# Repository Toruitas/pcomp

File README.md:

# Physical Computing 1

Msc Creative Computing 2019

Instructor: Phoenix Perry

By Stuart Leitch 

## Final Project:
Link: [Thinking Cap](https://github.com/Toruitas/thinkingcap)

## Homework & Labwork
[Week 1](https://github.com/Toruitas/pcomp/tree/master/wk01)

[Week 2](https://github.com/Toruitas/pcomp/tree/master/wk02)

[Week 3](https://github.com/Toruitas/pcomp/tree/master/wk03)

[Week 4](https://github.com/Toruitas/pcomp/tree/master/wk04)

Week 5 was pushed to week 6.

[Week 6](https://github.com/Toruitas/pcomp/tree/master/wk06)

[Week 7](https://github.com/Toruitas/pcomp/tree/master/wk07)

[Week 8 - group documentation of Feather](https://github.com/phoenixperry/cci-ual-pcomp/tree/master/week08/feather_docs)

[Week 9 - Eagle](https://github.com/Toruitas/pcomp/tree/master/wk09)

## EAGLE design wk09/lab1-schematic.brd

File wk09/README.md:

# Week 9 labs
Msc Creative Computing
Physical Computing #6 w/ Phoenix Perry
By Stuart Leitch
November 25, 2019

[Lecture PowerPoint](https://github.com/phoenixperry/cci-ual-pcomp/blob/master/week09/Tutorial_laserCutting.pdf)
[Lecture README](https://github.com/phoenixperry/cci-ual-pcomp/blob/master/week09/Week09.md)

## Lab #1: Learn Eagle via the tutorial

Eagle is a professional CAD software for designing circuitboards, which later go to fabrication. It's the next step beyond merely soldering.
Though it is professional, it doesn't actually install on Ubuntu. It just lives wherever you extract it to. 

Drawing a circuit was somewhat annoying, especially grabbing the center of each object to move or rotate. Still, given the large amount of obejcts included in the Sparkfun library, it was reasonably straightforward. Rather than use the suggested Arduino in the tutorial, I grabbed a MEGA from the collection to make things a bit more less copy and paste.

### The resulting circuit:

After drawing the circuit schematic, connecting the wires in a logical way proved to be its own challenge. Reminded me of those brain games where you have to route colored trains along tracks to their respective colored train garages. Eventually I got the whole circuit drawn on the board.

### The resulting board:

The primary question I have right now: Why is the board representation of the Arduino so dissimilar from the circuit diagram one? The only answer I can guess at is that this Arduino is only meant to be used on the circuit, and not used on the board side. In the future, when only using components, it may be clearer.

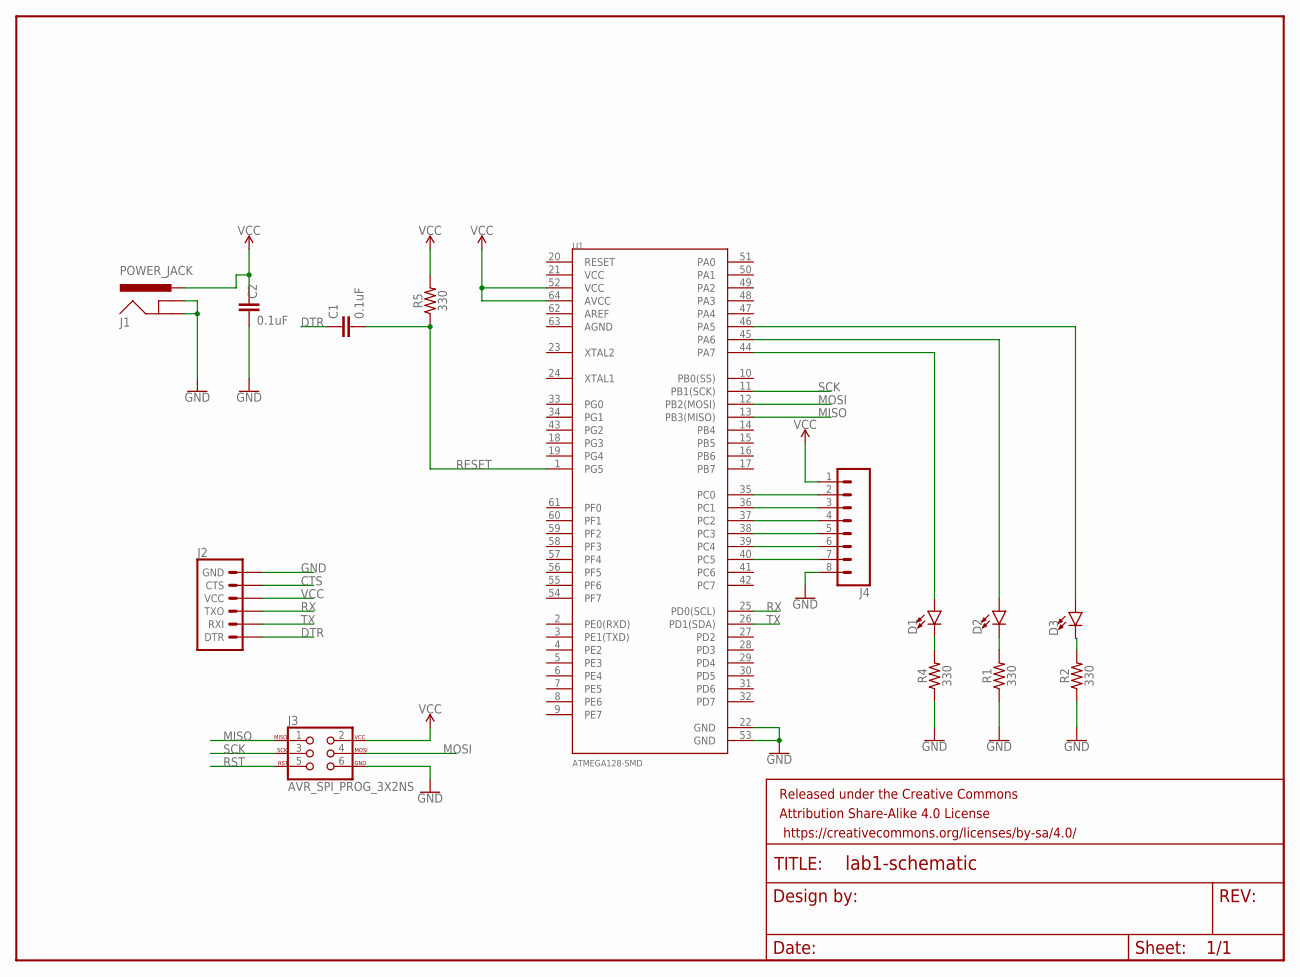
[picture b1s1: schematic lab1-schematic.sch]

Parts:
C1, C2: 0.1uF; CAP-PTH-SMALL-KIT
D1, D2, D3: LED3MM; LED_3MM
FRAME1: FRAME-LETTER; CREATIVE_COMMONS
J1: POWER_JACK; POWER_JACK_PTH
J2: 6_PIN_SERIAL_TARGET; 1X06
J3: AVR_SPI_PROG_3X2NS; 2X3-NS
J4: CONN_08"; 1X08
R1, R2, R4, R5: 330; AXIAL-0.3
U1: ATMEGA128-SMD; TQFP64_14X14MM

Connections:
CTS: J2.5 (CTS)
DTR: C1.1, J2.1 (DTR)
GND: C2.2, J1.GND, J1.GNDBREAK, J2.6 (GND), J3.6, J4.8, R1.P$1 (1), R2.P$1 (1), R4.P$1 (1), U1.22 (GND), U1.53 (GND)
MISO: J3.1, U1.13 (PB3(MISO))
MOSI: J3.4, U1.12 (PB2(MOSI))
unnamed: J4.2, U1.35 (PC0)
unnamed: J4.3, U1.36 (PC1)
unnamed: J4.4, U1.37 (PC2)
unnamed: J4.5, U1.38 (PC3)
unnamed: J4.6, U1.39 (PC4)
unnamed: J4.7, U1.40 (PC5)
unnamed: D2.A, U1.45 (PA6)
unnamed: D3.A, U1.46 (PA5)
unnamed: D1.A, U1.44 (PA7)
unnamed: D1.K (C), R4.P$2 (2)
unnamed: D2.K (C), R1.P$2 (2)
unnamed: D3.K (C), R2.P$2 (2)
RESET: C1.2, R5.P$1 (1), U1.1 (PG5)
RST: J3.5
RX: J2.3 (TXO), U1.25 (PD0(SCL))
SCK: J3.3, U1.11 (PB1(SCK))
TX: J2.2 (RXI), U1.26 (PD1(SDA))
VCC: C2.1, J1.PWR, J2.4 (VCC), J3.2, J4.1, R5.P$2 (2), U1.52 (VCC), U1.64 (AVCC)

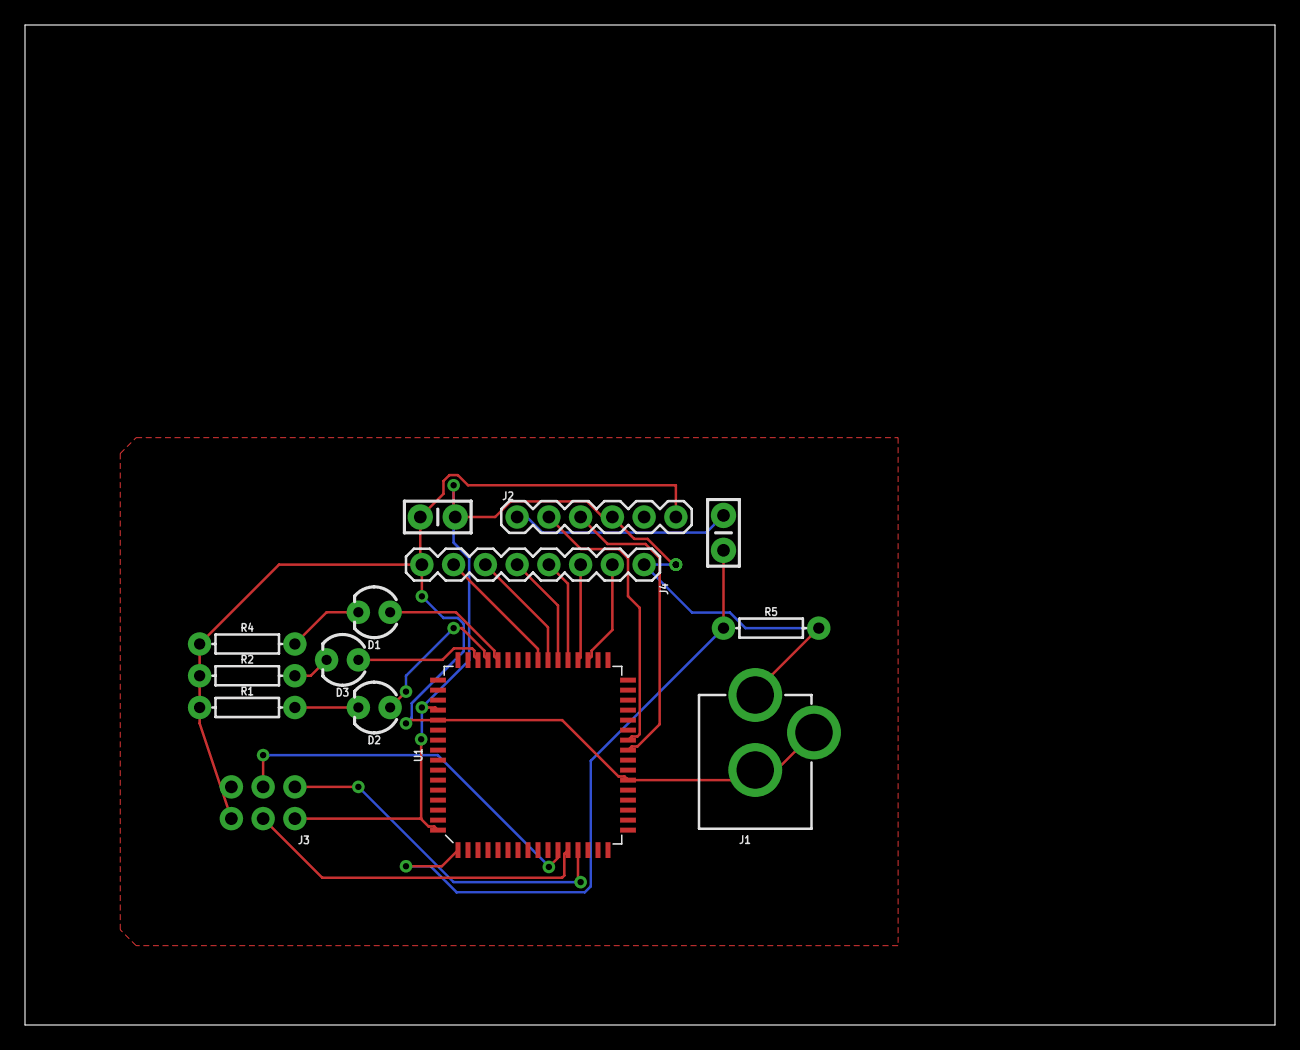
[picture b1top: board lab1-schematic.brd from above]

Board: 2 copper layers, 100.0 x 80.0 mm, 15 parts (0 on the bottom side), 21 nets.

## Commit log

2019-10-18 First commit after putting all pcomp work in single repo
2019-10-18 Readmes updated for new image filepaths.
2019-10-18 Update the updated image URLs for wks 1-3
2019-10-18 Added top-level README.md for easier navigation
2019-10-18 Formatting
2019-10-24 Add week 4's labs.
2019-10-24 Fix formatting on base readme
2019-10-24 Attempting to fix image orientation in wk 4 readme
2019-11-03 Added link to Final Project in root readme
2019-11-10 Add week 6 lab README
2019-11-17 Add week 7 to labs
2019-12-02 Rename folders. Add wk 9.
2019-12-02 Add images.
2019-12-02 Fix links to renamed folders.

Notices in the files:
parts and their libraries:
SparkFun-Capacitors: Licensing: Creative Commons ShareAlike 4.0 International - https://creativecommons.org/licenses/by-sa/4.0
SparkFun-Aesthetics: Released under the Creative Commons Attribution Share-Alike 4.0 License
SparkFun-Aesthetics: https://creativecommons.org/licenses/by-sa/4.0
